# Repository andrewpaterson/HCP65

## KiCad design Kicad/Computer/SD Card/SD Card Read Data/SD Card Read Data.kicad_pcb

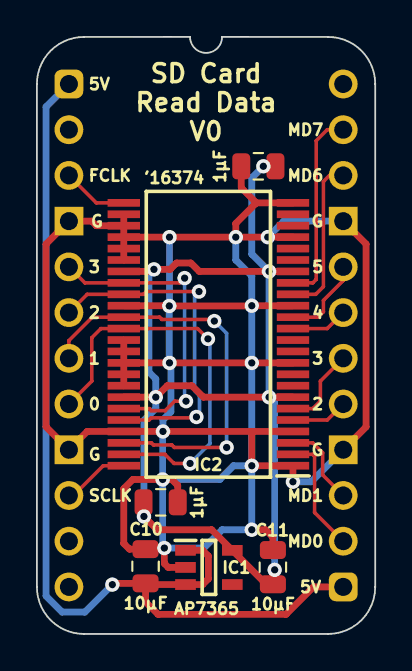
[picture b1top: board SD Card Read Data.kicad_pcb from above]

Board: 2 copper layers, 18.8 x 33.2 mm, 7 parts (0 on the bottom side), 17 nets.

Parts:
C1, C4: 1μF; C_0805
C10, C11: 10μF; C_0805
IC1: AP7365-33WG-7; SOT95P285X130-5N
IC2: 74LVC16374ADL; SOP64P1025X280-48N
J1: Board 2x12 W15.24mm; DIP-24_Board_W15.24mm

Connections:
5V: C10.1, IC1.1 (6VIn), IC1.3 (EN), J1.1, J1.13
/3.3V: C1.1, C4.1, C11.1, IC1.5 (3.3VOut), IC2.7 (3V), IC2.18 (3V), IC2.31 (3V), IC2.42 (3V)
DAT0: IC2.36 (2D0), IC2.47 (1D0), J1.8
DAT1: IC2.35 (2D1), IC2.46 (1D1), J1.7
DAT2: IC2.33 (2D2), IC2.44 (1D2), J1.6
DAT3: IC2.32 (2D3), IC2.43 (1D3), J1.5
First CLK: IC2.25 (2CP), J1.3
GND: C1.2, C4.2, C10.2, C11.2, IC1.2 (GND), IC2.1 (1~OE), IC2.4 (GND), IC2.10 (GND), IC2.15 (GND), IC2.21 (GND), IC2.24 (2~OE), IC2.26 (2D7), IC2.27 (2D6), IC2.28 (GND), IC2.29 (2D5), IC2.30 (2D4), IC2.34 (GND), IC2.37 (1D7), IC2.38 (1D6), IC2.39 (GND), IC2.40 (1D5), IC2.41 (1D4), IC2.45 (GND), J1.4, J1.9, J1.16, J1.21
MD0: IC2.2 (1Q0), J1.14
MD1: IC2.3 (1Q1), J1.15
MD2: IC2.5 (1Q2), J1.17
MD3: IC2.6 (1Q3), J1.18
MD4: IC2.13 (2Q0), J1.19
MD5: IC2.14 (2Q1), J1.20
MD6: IC2.16 (2Q2), J1.22
MD7: IC2.17 (2Q3), J1.23
Second CLK: IC2.48 (1CP), J1.10

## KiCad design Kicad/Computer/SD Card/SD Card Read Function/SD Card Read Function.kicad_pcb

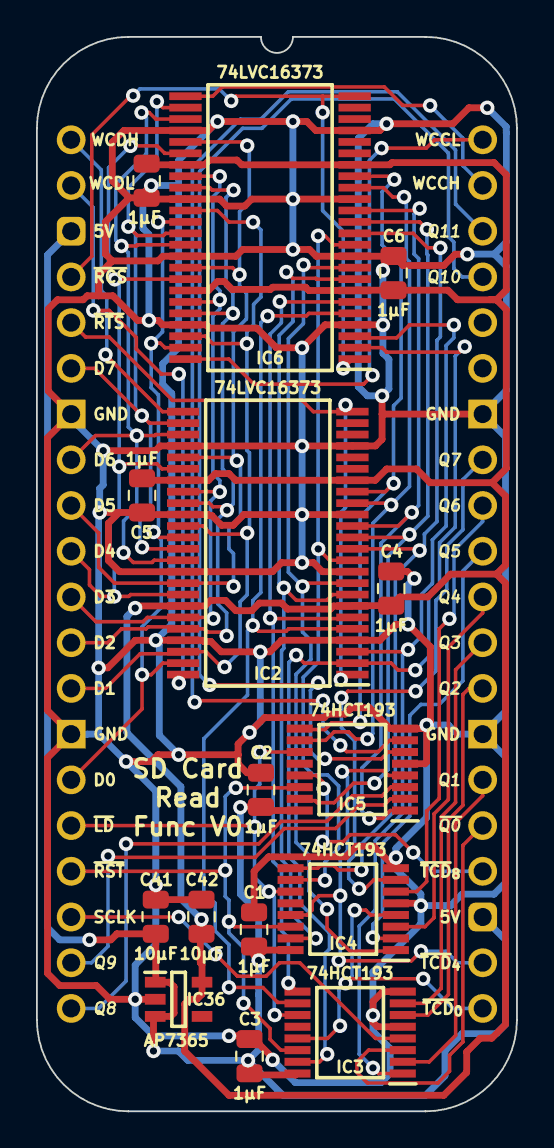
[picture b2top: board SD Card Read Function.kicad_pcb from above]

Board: 2 copper layers, 26.7 x 59.7 mm, 16 parts (0 on the bottom side), 47 nets.

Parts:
C1, C2, C3, C4, C5, C6, C7: 1μF; C_0805
C41, C42: 10μF; C_0805
IC2, IC6: 74LVC16373ADL,118; SOP64P1025X280-48N
IC3, IC4, IC5: 74HCT193PW,118; SOP65P640X110-16N
IC36: AP7365-33WG-7; SOT95P285X130-5N
J7: Board 2x20 W22.86mm; DIP-40_Board_W22.86mm

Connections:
5V: C1.1, C2.1, C3.1, C41.1, IC3.16 (5V), IC4.16 (5V), IC5.16 (5V), IC36.1 (6VIn), IC36.3 (EN), J7.3, J7.23
/3.3V: C4.1, C5.1, C6.1, C7.1, C42.1, IC2.7 (3V), IC2.18 (3V), IC2.31 (3V), IC2.42 (3V), IC6.7 (3V), IC6.18 (3V), IC6.31 (3V), IC6.42 (3V), IC36.5 (3.3VOut)
/CPL_{0}: IC2.2 (1Q0), IC3.15 (D0), IC6.2 (1Q0)
/CPL_{1}: IC2.3 (1Q1), IC3.1 (D1), IC6.3 (1Q1)
/CPL_{2}: IC2.5 (1Q2), IC3.10 (D2), IC6.5 (1Q2)
/CPL_{3}: IC2.6 (1Q3), IC3.9 (D3), IC6.6 (1Q3)
/CPL_{4}: IC2.8 (1Q4), IC4.15 (D0), IC6.8 (1Q4)
/CPL_{5}: IC2.9 (1Q5), IC4.1 (D1), IC6.9 (1Q5)
/CPL_{6}: IC2.11 (1Q6), IC4.10 (D2), IC6.11 (1Q6)
/CPL_{7}: IC2.12 (1Q7), IC4.9 (D3), IC6.12 (1Q7)
/CPL_{8}: IC2.13 (2Q0), IC5.15 (D0), IC6.13 (2Q0)
/CPL_{9}: IC2.14 (2Q1), IC5.1 (D1), IC6.14 (2Q1)
/CPL_{10}: IC2.16 (2Q2), IC5.10 (D2), IC6.16 (2Q2)
/CPL_{11}: IC2.17 (2Q3), IC5.9 (D3), IC6.17 (2Q3)
D0: IC2.36 (2D0), IC2.47 (1D0), IC6.36 (2D0), IC6.47 (1D0), J7.15
D1: IC2.35 (2D1), IC2.46 (1D1), IC6.35 (2D1), IC6.46 (1D1), J7.13
D2: IC2.33 (2D2), IC2.44 (1D2), IC6.33 (2D2), IC6.44 (1D2), J7.12
D3: IC2.32 (2D3), IC2.43 (1D3), IC6.32 (2D3), IC6.43 (1D3), J7.11
D4: IC2.30 (2D4), IC2.41 (1D4), IC6.30 (2D4), IC6.41 (1D4), J7.10
D5: IC2.29 (2D5), IC2.40 (1D5), IC6.29 (2D5), IC6.40 (1D5), J7.9
D6: IC2.27 (2D6), IC2.38 (1D6), IC6.27 (2D6), IC6.38 (1D6), J7.8
D7: IC2.26 (2D7), IC2.37 (1D7), IC6.26 (2D7), IC6.37 (1D7), J7.6
GND: C1.2, C2.2, C3.2, C4.2, C5.2, C6.2, C7.2, C41.2, C42.2, IC2.4 (GND), IC2.10 (GND), IC2.15 (GND), IC2.21 (GND), IC2.28 (GND), IC2.34 (GND), IC2.39 (GND), IC2.45 (GND), IC3.5 (CPU), IC3.8 (GND), IC4.5 (CPU), IC4.8 (GND), IC5.5 (CPU), IC5.8 (GND), IC6.4 (GND), IC6.10 (GND), IC6.15 (GND), IC6.21 (GND), IC6.28 (GND), IC6.34 (GND), IC6.39 (GND), IC6.45 (GND), IC36.2 (GND), J7.7, J7.14, J7.27, J7.34
Q0: IC3.3 (Q0), J7.25
Q1: IC3.2 (Q1), J7.26
Q2: IC3.6 (Q2), J7.28
Q3: IC3.7 (Q3), J7.29
Q4: IC4.3 (Q0), J7.30
Q5: IC4.2 (Q1), J7.31
Q6: IC4.6 (Q2), J7.32
Q7: IC4.7 (Q3), J7.33
Q8: IC5.3 (Q0), J7.20
Q9: IC5.2 (Q1), J7.19
Q10: IC5.6 (Q2), J7.37
Q11: IC5.7 (Q3), J7.38
Second Half CLK: IC3.4 (CPD), J7.18
Write Count CRC Byte High: IC6.25 (2LE), J7.39
Write Count CRC Byte Low: IC6.48 (1LE), J7.40
Write Count Data Byte High: IC2.25 (2LE), J7.1
Write Count Data Byte Low: IC2.48 (1LE), J7.2
~Load Down Count: IC3.11 (~PL), IC4.11 (~PL), IC5.11 (~PL), J7.16
~Read CRC Started: IC6.1 (1~OE), IC6.24 (2~OE), J7.4
~Read Transmit Started: IC2.1 (1~OE), IC2.24 (2~OE), J7.5
~Reset: IC3.14 (MR), IC4.14 (MR), IC5.14 (MR), J7.17
~TCD_{0..3}: IC3.13 (~TCD), IC4.4 (CPD), J7.21
~TCD_{4..7}: IC4.13 (~TCD), IC5.4 (CPD), J7.22
~TCD_{8..11}: IC5.13 (~TCD), J7.24

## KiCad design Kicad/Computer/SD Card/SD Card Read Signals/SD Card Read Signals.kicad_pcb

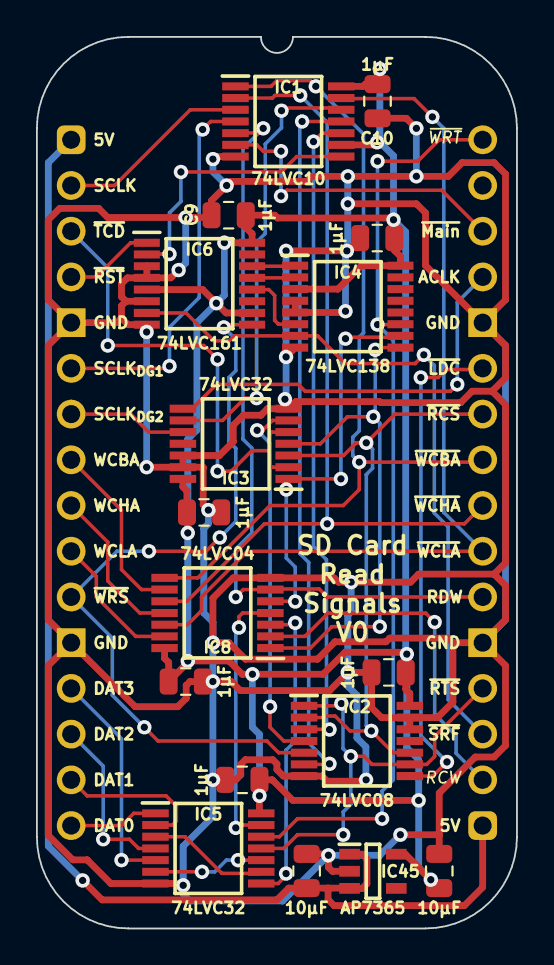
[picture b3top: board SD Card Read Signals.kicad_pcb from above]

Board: 2 copper layers, 26.7 x 49.5 mm, 18 parts (0 on the bottom side), 42 nets.

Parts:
C1, C4, C5, C6, C9, C10, C11: 1μF; C_0805
C2, C3: 10μF; C_0805
IC1: SN74LVC10APWR; SOP65P640X120-14N
IC2: 74LVC08APW,112; SOP65P640X110-14N
IC3, IC5: 74LVC32APW,118; SOP65P640X110-14N
IC4: 74LVC138APW-Q100J; SOP65P640X110-16N
IC6: 74LVC161PW,112; SOP65P640X110-16N
IC8: 74LVC04APW,118; SOP65P640X110-14N
IC45: AP7365-33WG-7; SOT95P285X130-5N
J8: Board 2x16 W22.86mm; DIP-32_Board_W22.86mm

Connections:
5V: C3.1, IC45.1 (6VIn), IC45.3 (EN), J8.1, J8.17
/3.3V: C1.1, C2.1, C4.1, C5.1, C6.1, C9.1, C10.1, C11.1, IC1.9 (3A), IC1.14 (3V), IC2.14 (3V), IC3.14 (3V), IC4.3 (A2), IC4.16 (3V), IC5.14 (3V), IC6.5 (D2), IC6.10 (CET), IC6.16 (3V), IC8.14 (3V), IC45.5 (3.3VOut)
/DAT0+DAT1: IC5.3 (1Y), IC5.9 (3A)
/DAT2+DAT3: IC5.6 (2Y), IC5.10 (3B)
/DAT_{0..3} Zero: IC5.8 (3Y), IC8.3 (2A)
/Funk0: IC4.1 (A0), IC6.14 (Q0)
/Funk1: IC4.2 (A1), IC6.13 (Q1)
/Funk2: IC4.6 (E3), IC6.12 (Q2)
/Read Funk Clock: IC1.8 (3Y), IC6.2 (CP)
/Write Count Address: IC1.12 (1Y), IC3.9 (3A)
/~DAT_{0..3 Zero}: IC5.13 (4B), IC8.4 (2Y)
/~RTS•~RCRCS: IC1.10 (3B), IC2.3 (1Y)
/~Read CRC Wide: IC3.4 (2A), IC4.9 (~Y6), IC8.1 (1A)
/~Read Data Wide: IC3.1 (1A), IC4.10 (~Y5), IC8.5 (3A)
/~SRFS•~WCSS: IC1.11 (3C), IC2.6 (2Y)
/~Stop Read Funk Started: IC2.4 (2A), IC3.6 (2Y)
Address CLK: IC3.8 (3Y), J8.29
DAT0: IC5.1 (1A), J8.16
DAT1: IC5.2 (1B), J8.15
DAT2: IC5.4 (2A), J8.14
DAT3: IC5.5 (2B), J8.13
GND: C1.2, C2.2, C3.2, C4.2, C5.2, C6.2, C9.2, C10.2, C11.2, IC1.7 (GND), IC2.7 (GND), IC2.12 (4A), IC2.13 (4B), IC3.7 (GND), IC3.12 (4A), IC3.13 (4B), IC4.4 (~E1), IC4.5 (~E2), IC4.8 (GND), IC5.7 (GND), IC6.3 (D0), IC6.4 (D1), IC6.6 (D3), IC6.8 (GND), IC8.7 (GND), IC45.2 (GND), J8.5, J8.12, J8.21, J8.28
Read CRC Wide: IC8.2 (1Y), J8.18
Read Data Wide: IC1.5 (2C), IC8.6 (3Y), J8.22
Second Half CLK: IC1.3 (2A), J8.2
Write Count Bank Address: IC8.9 (4A), J8.8
Write Count High Address: IC8.11 (5A), J8.9
Write Count Low Address: IC8.13 (6A), J8.10
~Load Down Count: IC2.8 (3Y), J8.27
~Main: IC1.6 (2Y), J8.30
~Read CRC Started: IC2.2 (1B), IC2.10 (3B), IC3.3 (1Y), J8.26
~Read Transmit Started: IC2.1 (1A), IC2.9 (3A), IC5.11 (4Y), J8.20
~Reset: IC6.1 (~MR), J8.4
~Second Half CLK_{Dragged1}: IC1.4 (2B), J8.6
~Second Half CLK_{Dragged2}: IC3.10 (3B), J8.7
~Stop Read Funk: IC4.7 (~Y7), IC6.7 (CEP), J8.19
~TCD_{8..11}: IC3.2 (1B), IC3.5 (2B), J8.3
~Wait For Read Transmit: IC4.11 (~Y4), IC5.12 (4A), J8.32
~Write Count Bank Address: IC1.1 (1A), IC8.8 (4Y), J8.25
~Write Count High Address: IC1.2 (1B), IC8.10 (5Y), J8.24
~Write Count Low Address: IC1.13 (1C), IC8.12 (6Y), J8.23
~Write Read Start: IC2.5 (2B), IC6.9 (~PE), J8.11

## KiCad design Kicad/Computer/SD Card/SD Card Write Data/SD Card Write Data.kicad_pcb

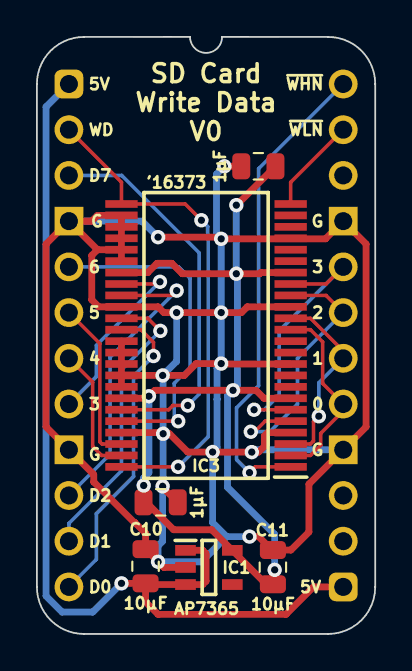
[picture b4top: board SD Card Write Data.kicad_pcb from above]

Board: 2 copper layers, 18.8 x 33.2 mm, 7 parts (0 on the bottom side), 18 nets.

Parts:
C1, C4: 1μF; C_0805
C10, C11: 10μF; C_0805
IC1: AP7365-33WG-7; SOT95P285X130-5N
IC3: 74LVC16373ADL,118; SOP64P1025X280-48N
J1: Board 2x12 W15.24mm; DIP-24_Board_W15.24mm

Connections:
5V: C10.1, IC1.1 (6VIn), IC1.3 (EN), J1.1, J1.13
/3.3V: C1.1, C4.1, C11.1, IC1.5 (3.3VOut), IC3.7 (3V), IC3.18 (3V), IC3.31 (3V), IC3.42 (3V)
D0: IC3.36 (2D0), J1.12
D1: IC3.35 (2D1), J1.11
D2: IC3.33 (2D2), J1.10
D3: IC3.32 (2D3), J1.8
D4: IC3.47 (1D0), J1.7
D5: IC3.46 (1D1), J1.6
D6: IC3.44 (1D2), J1.5
D7: IC3.43 (1D3), J1.3
DAT0: IC3.2 (1Q0), IC3.13 (2Q0), J1.17
DAT1: IC3.3 (1Q1), IC3.14 (2Q1), J1.18
DAT2: IC3.5 (1Q2), IC3.16 (2Q2), J1.19
DAT3: IC3.6 (1Q3), IC3.17 (2Q3), J1.20
GND: C1.2, C4.2, C10.2, C11.2, IC1.2 (GND), IC3.4 (GND), IC3.10 (GND), IC3.15 (GND), IC3.21 (GND), IC3.26 (2D7), IC3.27 (2D6), IC3.28 (GND), IC3.29 (2D5), IC3.30 (2D4), IC3.34 (GND), IC3.37 (1D7), IC3.38 (1D6), IC3.39 (GND), IC3.40 (1D5), IC3.41 (1D4), IC3.45 (GND), J1.4, J1.9, J1.16, J1.21
Write Data: IC3.25 (2LE), IC3.48 (1LE), J1.2
~Write High Nybble: IC3.1 (1~OE), J1.24
~Write Low Nybble: IC3.24 (2~OE), J1.23

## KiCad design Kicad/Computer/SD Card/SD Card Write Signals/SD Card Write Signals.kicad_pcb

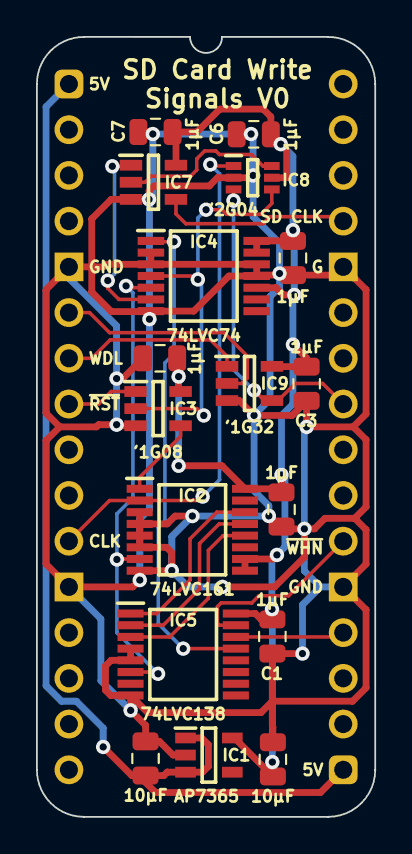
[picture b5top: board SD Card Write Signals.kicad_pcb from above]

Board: 2 copper layers, 18.8 x 43.3 mm, 18 parts (0 on the bottom side), 20 nets.

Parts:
C1, C2, C3, C4, C5, C6, C7: 1μF; C_0805
C10, C11: 10μF; C_0805
IC1: AP7365-33WG-7; SOT95P285X130-5N
IC2: 74LVC161PW,112; SOP65P640X110-16N
IC3: 74LVC1G08GV,125; SOT95P275X110-5N
IC4: 74LVC74APW,118; SOP65P640X110-14N
IC5: 74LVC138APW-Q100J; SOP65P640X110-16N
IC7: 74LVC1G125GV-Q100; SOT95P275X110-5N
IC8: 74LVC2G04GW-Q100H; SOP65P210X110-6N
IC9: 74LVC1G32GV,125; SOT95P275X110-5N
J1: Board 2x16 W15.24mm; DIP-32_Board_W15.24mm

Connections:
5V: C10.1, IC1.1 (6VIn), IC1.3 (EN), J1.1, J1.17
/3.3V: C1.1, C2.1, C3.1, C4.1, C5.1, C6.1, C7.1, C11.1, IC1.5 (3.3VOut), IC2.9 (~PE), IC2.10 (CET), IC2.16 (3V), IC3.5 (3V), IC4.10 (~2SD), IC4.13 (~2RD), IC4.14 (3V), IC5.16 (3V), IC7.5 (3V), IC8.5 (3V), IC9.5 (3V)
/Nybble A0: IC2.14 (Q0), IC5.1 (A0)
/Nybble A1: IC2.13 (Q1), IC5.2 (A1)
/Nybble A2: IC2.12 (Q2), IC5.3 (A2)
/SD Write: IC2.7 (CEP), IC4.5 (1Q), IC5.6 (E3)
/~Fast CLK: IC7.2 (A), IC8.6 (1Y)
/~Reset Write Counter: IC2.1 (~MR), IC3.4 (Y)
/~SD Write: IC4.6 (~1Q), IC7.1 (~OE)
/~Stop Write: IC4.1 (~1RD), IC5.13 (~Y2)
/~Write Data: IC3.2 (A), IC4.4 (~1SD), IC8.4 (2Y)
Fast CLK: IC2.2 (CP), IC8.1 (1A), J1.11
GND: C1.2, C2.2, C3.2, C4.2, C5.2, C6.2, C7.2, C10.2, C11.2, IC1.2 (GND), IC2.3 (D0), IC2.4 (D1), IC2.5 (D2), IC2.6 (D3), IC2.8 (GND), IC3.3 (GND), IC4.2 (1D), IC4.3 (1CP), IC4.7 (GND), IC4.11 (2CP), IC4.12 (2D), IC5.4 (~E1), IC5.5 (~E2), IC5.8 (GND), IC7.3 (GND), IC8.2 (GND), IC9.3 (GND), J1.5, J1.12, J1.21, J1.28
SD CLK: IC7.4 (Y), J1.29
Write Data: IC8.3 (2A), IC9.4 (Y), J1.25
Write Data High: IC9.2 (A), J1.6
Write Data Low: IC9.1 (B), J1.7
~Reset: IC3.1 (B), J1.8
~Write High Nybble: IC5.15 (~Y0), J1.22
~Write Low Nybble: IC5.14 (~Y1), J1.20

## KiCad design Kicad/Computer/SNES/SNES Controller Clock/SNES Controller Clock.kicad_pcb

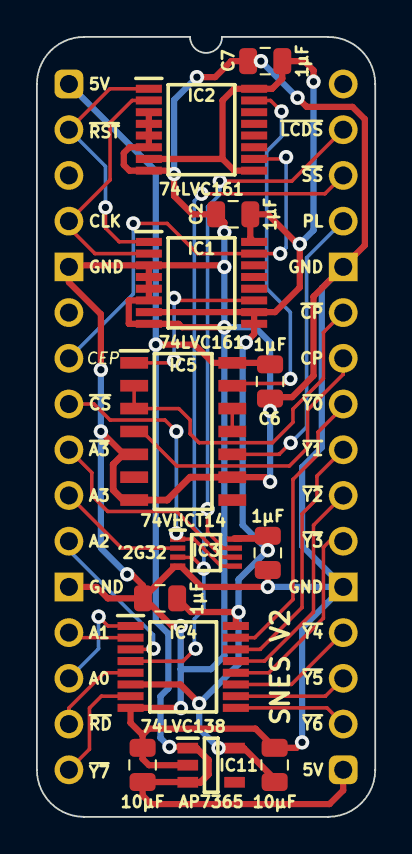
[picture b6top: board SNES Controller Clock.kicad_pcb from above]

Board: 2 copper layers, 18.8 x 43.3 mm, 14 parts (0 on the bottom side), 29 nets.

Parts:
C1, C2, C6, C7, C8: 1μF; C_0805
C9, C10: 10μF; C_0805
IC1, IC2: 74LVC161PW,112; SOP65P640X110-16N
IC3: 74LVC2G32DC-Q100H; SOP50P310X100-8N
IC4: 74LVC138APW-Q100J; SOP65P640X110-16N
IC5: 74VHCT14AM; SOIC127P600X175-14N
IC11: AP7365-33WG-7; SOT95P285X130-5N
J2: Board 2x16 W15.24mm; DIP-32_Board_W15.24mm

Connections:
5V: C6.1, C9.1, IC5.14 (5V), IC11.1 (6VIn), IC11.3 (EN), J2.1, J2.17
/3.3V: C1.1, C2.1, C7.1, C8.1, C10.1, IC1.7 (CEP), IC1.9 (~PE), IC1.10 (CET), IC1.16 (3V), IC2.7 (CEP), IC2.9 (~PE), IC2.16 (3V), IC3.8 (VCC), IC4.6 (E3), IC4.16 (3V), IC11.5 (3.3VOut)
/Serial CP: IC1.11 (Q3), IC5.1 (1A)
/Serial PL: IC2.15 (TC), IC5.13 (6A)
/~Serial PL: IC5.11 (5A), IC5.12 (6Y)
A0: IC4.1 (A0), J2.14
A1: IC4.2 (A1), J2.13
A2: IC4.3 (A2), J2.11
A3: IC3.2 (1B), J2.10
CEP: IC1.15 (TC), IC2.10 (CET), J2.7
CLK: IC1.2 (CP), IC2.2 (CP), J2.4
GND: C1.2, C2.2, C6.2, C7.2, C8.2, C9.2, C10.2, IC1.3 (D0), IC1.4 (D1), IC1.5 (D2), IC1.6 (D3), IC1.8 (GND), IC2.3 (D0), IC2.4 (D1), IC2.5 (D2), IC2.6 (D3), IC2.8 (GND), IC3.4 (GND), IC4.8 (GND), IC5.5 (3A), IC5.7 (GND), IC5.9 (4A), IC11.2 (GND), J2.5, J2.12, J2.21, J2.28
Serial CP_{2}: IC5.4 (2Y), J2.26
Serial PL_{2}: IC5.10 (5Y), J2.29
~A3: IC3.6 (2B), J2.9
~Device Registers: IC3.1 (1A), IC3.5 (2A), J2.8
~LCD Select: IC3.7 (1Y), J2.31
~RD: IC4.5 (~E2), J2.15
~Reset: IC1.1 (~MR), IC2.1 (~MR), J2.2
~Serial CP: IC5.2 (1Y), IC5.3 (2A), J2.27
~Serial Select: IC3.3 (2Y), IC4.4 (~E1), J2.30
~Y0: IC4.15 (~Y0), J2.25
~Y1: IC4.14 (~Y1), J2.24
~Y2: IC4.13 (~Y2), J2.23
~Y3: IC4.12 (~Y3), J2.22
~Y4: IC4.11 (~Y4), J2.20
~Y5: IC4.10 (~Y5), J2.19
~Y6: IC4.9 (~Y6), J2.18
~Y7: IC4.7 (~Y7), J2.16

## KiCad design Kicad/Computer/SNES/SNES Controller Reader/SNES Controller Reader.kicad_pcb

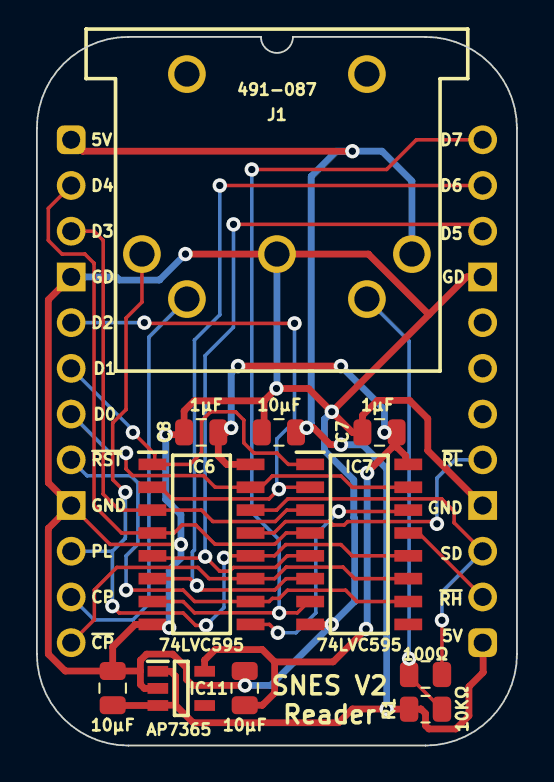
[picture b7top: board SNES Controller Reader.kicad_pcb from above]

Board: 2 copper layers, 26.7 x 39.4 mm, 12 parts (0 on the bottom side), 20 nets.

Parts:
C6, C9, C10: 10μF; C_0805
C7, C8: 1μF; C_0805
IC6, IC7: 74LVC595AD; SOIC127P600X175-16N
IC11: AP7365-33WG-7; SOT95P285X130-5N
J1: 491-087; 491087
J2: Board 2x12 W22.86mm; DIP-24_Board_W22.86mm
R1: 10KΩ; R_0805
R2: 100Ω; R_0805

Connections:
5V: C6.1, C9.1, IC11.1 (6VIn), IC11.3 (EN), J1.3, J2.1, J2.13, R1.2
/3.3V: C7.1, C8.1, C10.1, IC6.16 (3V), IC7.16 (3V), IC11.5 (3.3VOut)
/Q7S: IC6.9 (Q7S), IC7.14 (DS)
/Serial Data _{IN}: J1.5, R1.1, R2.1
D0: IC6.15 (Q0), IC7.15 (Q0), J2.7
D1: IC6.1 (Q1), IC7.1 (Q1), J2.6
D2: IC6.2 (Q2), IC7.2 (Q2), J2.5
D3: IC6.3 (Q3), IC7.3 (Q3), J2.3
D4: IC6.4 (Q4), IC7.4 (Q4), J2.2
D5: IC6.5 (Q5), IC7.5 (Q5), J2.22
D6: IC6.6 (Q6), IC7.6 (Q6), J2.23
D7: IC6.7 (Q7), IC7.7 (Q7), J2.24
GND: C6.2, C7.2, C8.2, C9.2, C10.2, IC6.8 (GND), IC7.8 (GND), IC11.2 (GND), J1.2, J2.4, J2.9, J2.16, J2.21
Serial CP: J1.4, J2.11
Serial Data: IC6.14 (DS), J2.15, R2.2
Serial PL: IC6.12 (STCP), IC7.12 (STCP), J1.1, J2.10
~Read High: IC7.13 (~OE), J2.14
~Read Low: IC6.13 (~OE), J2.17
~Reset: IC6.10 (~MR), IC7.10 (~MR), J2.8
~Serial CP: IC6.11 (SHCP), IC7.11 (SHCP), J2.12

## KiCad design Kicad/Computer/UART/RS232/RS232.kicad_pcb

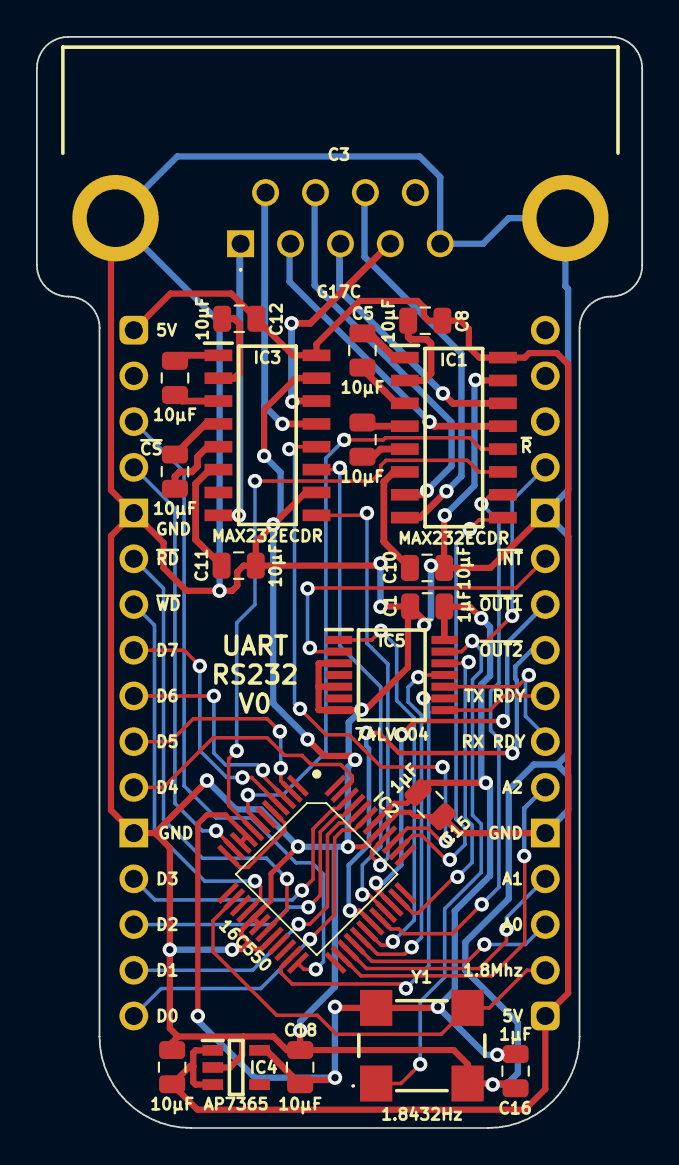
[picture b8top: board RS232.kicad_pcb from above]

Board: 2 copper layers, 33.6 x 60.6 mm, 21 parts (0 on the bottom side), 56 nets.

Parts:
C1, C15, C16: 1μF; C_0805
C3: G17C0900132EU
C4, C5, C8, C10, C11, C12, C13, C14: 10μF; C_0805
C17, C18: 10µF; C_0805
IC1, IC3: MAX232ECDR; SOIC127P600X175-16N
IC2: TL16C550DPTR; QFP50P900X900X160-48N
IC4: AP7365-33WG-7; SOT95P285X130-5N
IC5: 74LVC04APW,118; SOP65P640X110-14N
J1: Board 2x16 W22.86mm; DIP-32_Board_W22.86mm_Nak
Y1: LFSPXO020733

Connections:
1.8432MHz: IC2.14 (XIN), J1.18, Y1.3 (OUTPUT)
5V: C8.2, C12.2, C17.1, IC1.16 (5V), IC3.16 (5V), IC4.1 (6VIn), IC4.3 (EN), J1.1, J1.17
/3.3V: C1.1, C15.1, C16.1, C18.1, IC2.9 (CS0), IC2.10 (CS1), IC2.42 (5V), IC4.5 (3.3VOut), IC5.14 (3V), Y1.4 (3V)
/CD_{232}: C3.1, IC3.8 (RIN2)
/CTS_{232}: C3.8, IC1.8 (RIN2)
/DCD: IC2.40 (~DCD), IC3.9 (ROUT2)
/DSR_{232}: C3.6, IC3.13 (RIN1)
/DTR_{232}: C3.4, IC3.14 (TOUT1)
/INT: IC2.30 (INTRPT), IC5.1 (1A)
/RTS_{232}: C3.7, IC1.7 (TOUT2)
/RX_{232}: C3.2, IC1.13 (RIN1)
/Reset: IC2.35 (MR), IC5.12 (6Y)
/SIN: IC1.12 (ROUT1), IC2.7 (SIN)
/SOUT: IC1.11 (TIN1), IC2.8 (SOUT)
/TX_{232}: C3.3, IC1.14 (TOUT1)
/~CTS: IC1.9 (ROUT2), IC2.38 (~CTS)
/~DSR: IC2.39 (~DSR), IC3.12 (ROUT1)
/~DTR: IC2.33 (~DTR), IC3.11 (TIN1)
/~RTS: IC1.10 (TIN2), IC2.32 (~RTS)
/~RXRDY: IC2.29 (~RXRDY), IC5.11 (5A)
/~TXRDY: IC2.23 (~TXRDY), IC5.9 (4A)
A0: IC2.28 (A0), J1.19
A1: IC2.27 (A1), J1.20
A2: IC2.26 (A2), J1.22
D0: IC2.43 (D0), J1.16
D1: IC2.44 (D1), J1.15
D2: IC2.45 (D2), J1.14
D3: IC2.46 (D3), J1.13
D4: IC2.47 (D4), J1.11
D5: IC2.2 (D5), J1.10
D6: IC2.3 (D6), J1.9
D7: IC2.4 (D7), J1.8
GND: C1.2, C3.5, C3.MH1, C3.MH2, C10.1, C11.1, C15.2, C16.2, C17.2, C18.2, IC1.15 (GND), IC2.17 (WR2), IC2.18 (GND), IC2.20 (RD2), IC2.41 (~RI), IC3.10 (TIN2), IC3.15 (GND), IC4.2 (GND), IC5.3 (2A), IC5.5 (3A), IC5.7 (GND), J1.5, J1.12, J1.21, J1.28, Y1.2 (GND)
unnamed: C5.2, IC1.1 (C1+)
unnamed: C5.1, IC1.3 (C1-)
unnamed: C4.2, IC1.4 (C2+)
unnamed: C4.1, IC1.5 (C2-)
unnamed: C8.1, IC1.2 (VS+)
unnamed: C10.2, IC1.6 (VS-)
unnamed: IC2.5 (RCLK), IC2.12 (~BAUDOUT)
unnamed: C13.2, IC3.1 (C1+)
unnamed: C13.1, IC3.3 (C1-)
unnamed: C14.2, IC3.4 (C2+)
unnamed: C14.1, IC3.5 (C2-)
unnamed: C12.1, IC3.2 (VS+)
unnamed: C11.2, IC3.6 (VS-)
RX Ready: IC5.10 (5Y), J1.23
TX Ready: IC5.8 (4Y), J1.24
~ADS: IC2.24 (~ADS), J1.3
~CS: IC2.11 (~CS2), J1.4
~INT: IC5.2 (1Y), J1.27
~OUT1: IC2.34 (~OUT1), J1.26
~OUT2: IC2.31 (~OUT2), J1.25
~RD: IC2.19 (~RD1), J1.6
~Reset: IC5.13 (6A), J1.29, Y1.1 (EN)
~WD: IC2.16 (~WR1), J1.7
